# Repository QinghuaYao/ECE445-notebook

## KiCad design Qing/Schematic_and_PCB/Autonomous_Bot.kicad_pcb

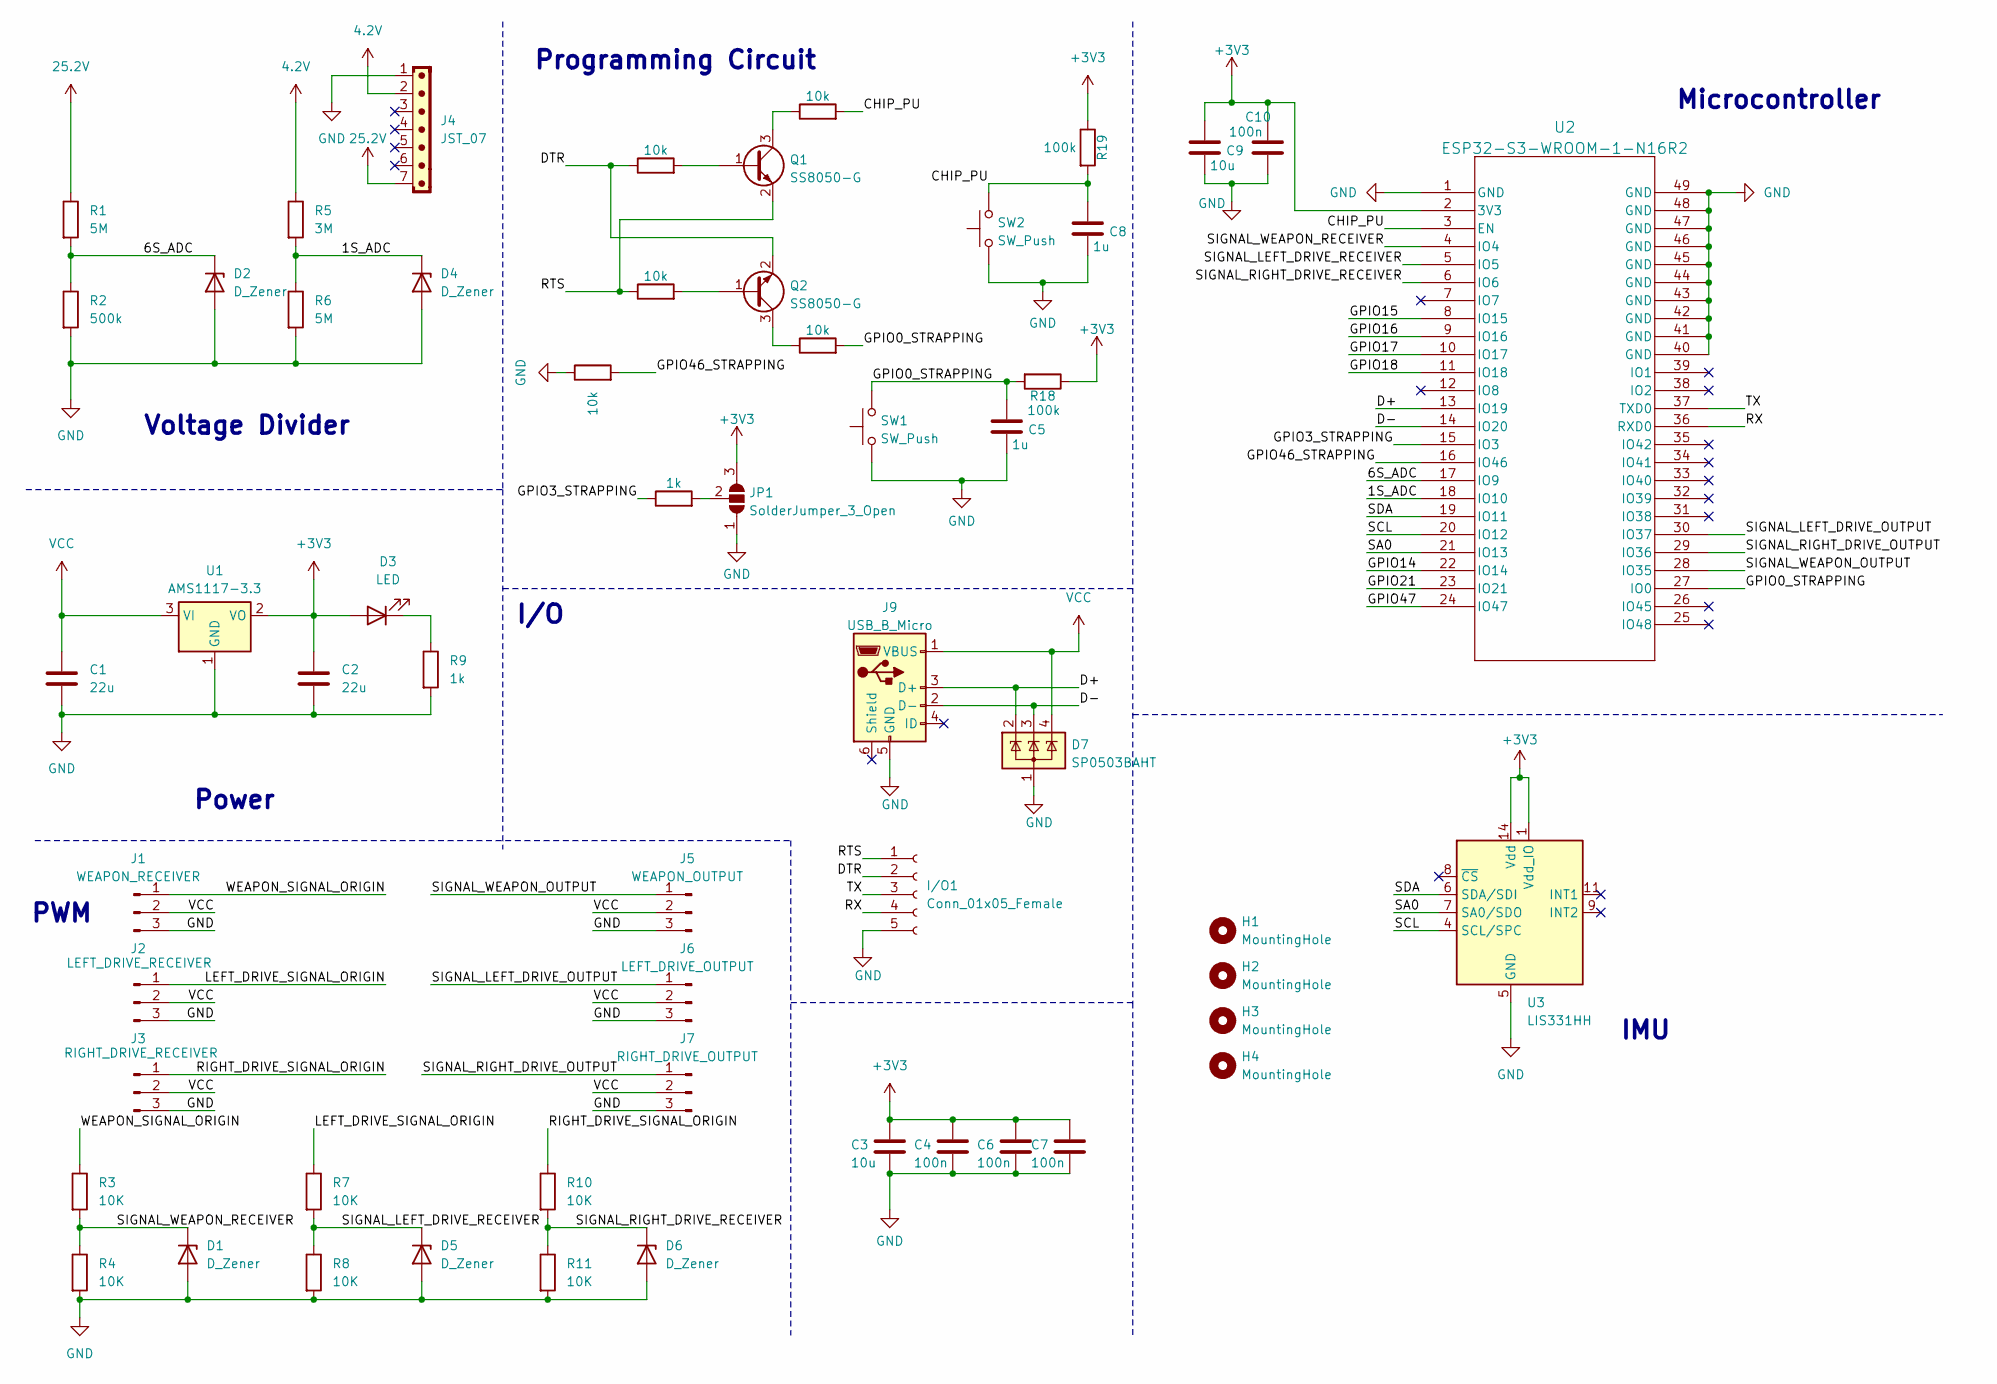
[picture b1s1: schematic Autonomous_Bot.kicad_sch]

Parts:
C1, C2: 22u; C_0603_1608Metric
C3: 10u; C_0603_1608Metric
C4, C6, C7: 100n; C_0603_1608Metric
C5, C8: 1u; C_0603_1608Metric
C9: 10u; C_0805_2012Metric
C10: 100n; C_0805_2012Metric
D1, D2, D4, D5, D6: D_Zener; D_0603_1608Metric
D3: LED; LED_0603_1608Metric
D7: SP0503BAHT; SOT-143
H1, H2, H3, H4: MountingHole; MountingHole_2.2mm_M2
I/O1: Conn_01x05_Female; PinHeader_1x05_P2.54mm_Vertical
J1: WEAPON_RECEIVER; PinHeader_1x03_P2.54mm_Vertical
J2: LEFT_DRIVE_RECEIVER; PinHeader_1x03_P2.54mm_Vertical
J3: RIGHT_DRIVE_RECEIVER; PinHeader_1x03_P2.54mm_Vertical
J4: JST_07; JST_EH_B7B-EH-A_1x07_P2.50mm_Vertical
J5: WEAPON_OUTPUT; PinHeader_1x03_P2.54mm_Vertical
J6: LEFT_DRIVE_OUTPUT; PinHeader_1x03_P2.54mm_Vertical
J7: RIGHT_DRIVE_OUTPUT; PinHeader_1x03_P2.54mm_Vertical
J9: USB_B_Micro; USB_Micro-B_Amphenol_10118194_Horizontal
JP1: SolderJumper_3_Open; SolderJumper-3_P2.0mm_Open_TrianglePad1.0x1.5mm
Q1, Q2: SS8050-G; SOT-23
R1, R6: 5M; R_1206_3216Metric
R2: 500k; R_0805_2012Metric
R3, R4, R7, R8, R10, R11: 10K; R_1206_3216Metric
R5: 3M; R_0603_1608Metric
R9: 1k; R_0603_1608Metric
R12, R13, R14, R16, R17: 10k; R_0805_2012Metric
R15: 1k; R_0805_2012Metric
R18: 100k; R_0805_2012Metric
R19: 100k; R_0603_1608Metric
SW1, SW2: SW_Push; SW_SPST_B3S-1000
U1: AMS1117-3.3; SOT-223-3_TabPin2
U2: ESP32-S3-WROOM-1-N16R2; ESP32-S3-WROOM-1_EXP
U3: LIS331HH; LGA-16_3x3mm_P0.5mm_LayoutBorder3x5y

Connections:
4.2V: J4.2, R5.1
25.2V: J4.7, R1.1
+3V3: C2.1, C3.1, C4.1, C6.1, C7.1, C9.1, C10.1, D3.2 (A), JP1.3 (B), R18.1, R19.1, U1.2 (VO), U2.2 (3V3), U3.1 (Vdd_IO), U3.14 (Vdd), U3.15 (Vdd)
/1S_ADC: D4.1 (K), R5.2, R6.1, U2.18 (IO10)
/6S_ADC: D2.1 (K), R1.2, R2.1, U2.17 (IO9)
/CHIP_PU: C8.1, R16.2, R19.2, SW2.2, U2.3 (EN)
/D+: D7.2 (K), J9.3 (D+), U2.13 (IO19)
/D-: D7.3 (K), J9.2 (D-), U2.14 (IO20)
/DTR: I/O1.2, Q2.2 (E), R13.1
/GPIO0_STRAPPING: C5.1, R17.2, R18.2, SW1.2, U2.27 (IO0)
/GPIO3_STRAPPING: R15.1, U2.15 (IO3)
/GPIO14: U2.22 (IO14)
/GPIO15: U2.8 (IO15)
/GPIO16: U2.9 (IO16)
/GPIO17: U2.10 (IO17)
/GPIO18: U2.11 (IO18)
/GPIO21: U2.23 (IO21)
/GPIO46_STRAPPING: R12.2, U2.16 (IO46)
/GPIO47: U2.24 (IO47)
/LEFT_DRIVE_SIGNAL_ORIGIN: J2.1, R7.1
/RIGHT_DRIVE_SIGNAL_ORIGIN: J3.1, R10.1
/RTS: I/O1.1, Q1.2 (E), R14.1
/RX: I/O1.4, U2.36 (RXD0)
/SA0: U2.21 (IO13), U3.7 (SA0/SDO)
/SCL: U2.20 (IO12), U3.4 (SCL/SPC)
/SDA: U2.19 (IO11), U3.6 (SDA/SDI)
/SIGNAL_LEFT_DRIVE_OUTPUT: J6.1, U2.30 (IO37)
/SIGNAL_LEFT_DRIVE_RECEIVER: D5.1 (K), R7.2, R8.1, U2.5 (IO5)
/SIGNAL_RIGHT_DRIVE_OUTPUT: J7.1, U2.29 (IO36)
/SIGNAL_RIGHT_DRIVE_RECEIVER: D6.1 (K), R10.2, R11.1, U2.6 (IO6)
/SIGNAL_WEAPON_OUTPUT: J5.1, U2.28 (IO35)
/SIGNAL_WEAPON_RECEIVER: D1.1 (K), R3.2, R4.1, U2.4 (IO4)
/TX: I/O1.3, U2.37 (TXD0)
/WEAPON_SIGNAL_ORIGIN: J1.1, R3.1
GND: C1.2, C2.2, C3.2, C4.2, C5.2, C6.2, C7.2, C8.2, C9.2, C10.2, D1.2 (A), D2.2 (A), D4.2 (A), D5.2 (A), D6.2 (A), D7.1 (A), I/O1.5, J1.3, J2.3, J3.3, J4.1, J5.3, J6.3, J7.3, J9.5 (GND), JP1.1 (A), R2.2, R4.2, R6.2, R8.2, R9.2, R11.2, R12.1, SW1.1, SW2.1, U1.1 (GND), U2.1 (GND), U2.40 (GND), U2.41 (GND), U2.42 (GND), U2.43 (GND), U2.44 (GND), U2.45 (GND), U2.46 (GND), U2.47 (GND), U2.48 (GND), U2.49 (GND), U3.5 (GND), U3.10 (GND), U3.12 (GND), U3.13 (GND), U3.16 (GND)
unnamed: D3.1 (K), R9.1
unnamed: JP1.2 (C), R15.2
unnamed: Q1.1 (B), R13.2
unnamed: Q1.3 (C), R16.1
unnamed: Q2.1 (B), R14.2
unnamed: Q2.3 (C), R17.1
VCC: C1.1, D7.4 (K), J1.2, J2.2, J3.2, J5.2, J6.2, J7.2, J9.1 (VBUS), U1.3 (VI)

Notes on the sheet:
Power
IMU
Programming Circuit
Microcontroller
PWM
I/O
Voltage Divider

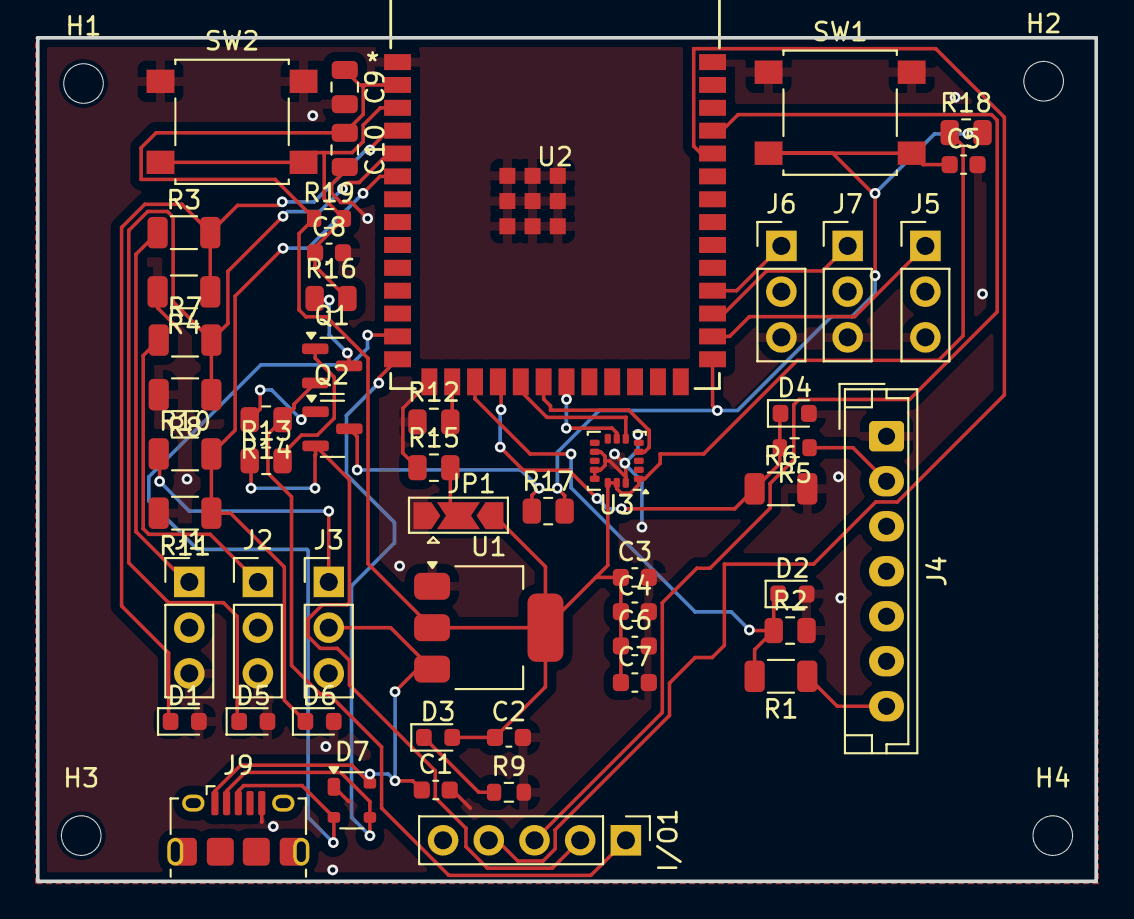
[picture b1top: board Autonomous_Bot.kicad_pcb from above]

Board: 2 copper layers, 58.8 x 46.9 mm, 57 parts (0 on the bottom side), 35 nets.

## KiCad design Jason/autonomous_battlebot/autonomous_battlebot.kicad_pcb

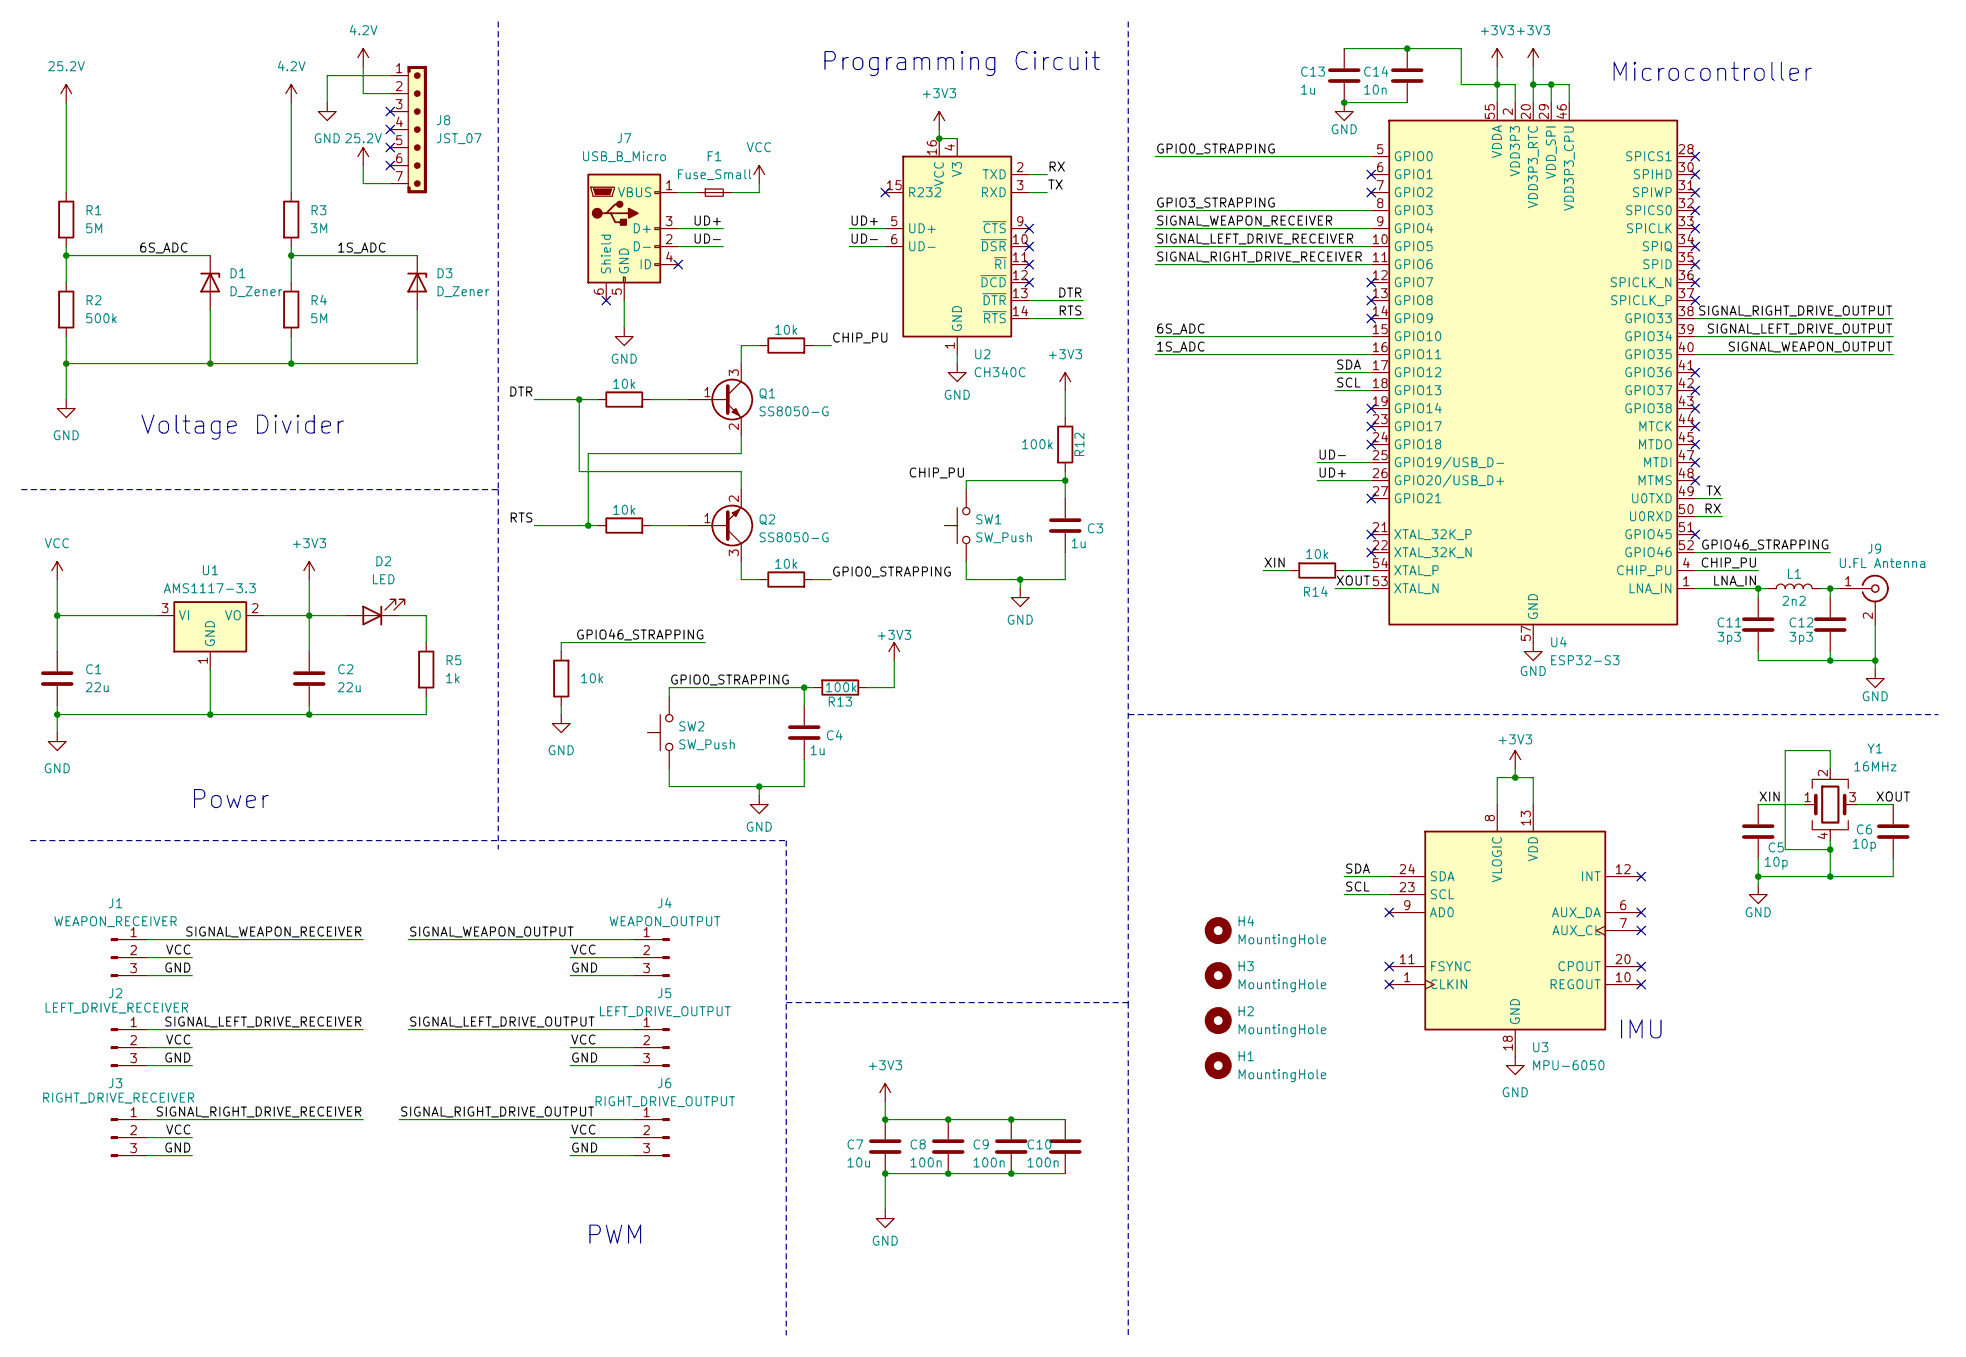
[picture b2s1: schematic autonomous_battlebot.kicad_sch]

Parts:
C1, C2: 22u; C_0603_1608Metric
C3, C4, C13: 1u; C_0603_1608Metric
C5, C6: 10p; C_0603_1608Metric
C7: 10u; C_0603_1608Metric
C8, C9, C10: 100n; C_0603_1608Metric
C11, C12: 3p3; C_0603_1608Metric
C14: 10n; C_0603_1608Metric
D1, D3: D_Zener; D_0603_1608Metric
D2: LED; LED_0603_1608Metric
F1: Fuse_Small; Fuse_0603_1608Metric
H1, H2, H3, H4: MountingHole; MountingHole_2.2mm_M2
J1: WEAPON_RECEIVER; PinHeader_1x03_P2.54mm_Vertical
J2: LEFT_DRIVE_RECEIVER; PinHeader_1x03_P2.54mm_Vertical
J3: RIGHT_DRIVE_RECEIVER; PinHeader_1x03_P2.54mm_Vertical
J4: WEAPON_OUTPUT; PinHeader_1x03_P2.54mm_Vertical
J5: LEFT_DRIVE_OUTPUT; PinHeader_1x03_P2.54mm_Vertical
J6: RIGHT_DRIVE_OUTPUT; PinHeader_1x03_P2.54mm_Vertical
J7: USB_B_Micro; USB_Micro-B_Molex-105017-0001
J8: JST_07; JST_EH_B7B-EH-A_1x07_P2.50mm_Vertical
J9: U.FL Antenna; U.FL_Molex_MCRF_73412-0110_Vertical
L1: 2n2; L_0603_1608Metric
Q1, Q2: SS8050-G; SOT-23
R1, R4: 5M; R_1206_3216Metric
R2: 500k; R_0805_2012Metric
R3: 3M; R_0603_1608Metric
R5: 1k; R_0603_1608Metric
R7, R8, R9, R10, R11, R14: 10k; R_0805_2012Metric
R12: 100k; R_0603_1608Metric
R13: 100k; R_0805_2012Metric
SW1, SW2: SW_Push; SW_SPST_B3S-1000
U1: AMS1117-3.3; SOT-223-3_TabPin2
U2: CH340C; SOIC-16_3.9x9.9mm_P1.27mm
U3: MPU-6050; InvenSense_QFN-24_4x4mm_P0.5mm
U4: ESP32-S3; QFN-56-1EP_7x7mm_P0.4mm_EP4x4mm
Y1: 16MHz; Crystal_SMD_3225-4Pin_3.2x2.5mm

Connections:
4.2V: J8.2, R3.1
25.2V: J8.7, R1.1
+3V3: C2.1, C7.1, C8.1, C9.1, C10.1, C13.1, C14.1, D2.2 (A), R12.1, R13.1, U1.2 (VO), U2.4 (V3), U2.16 (VCC), U3.8 (VLOGIC), U3.13 (VDD), U4.2 (VDD3P3), U4.3 (VDD3P3), U4.20 (VDD3P3_RTC), U4.29 (VDD_SPI), U4.46 (VDD3P3_CPU), U4.55 (VDDA), U4.56 (VDDA)
/1S_ADC: D3.1 (K), R3.2, R4.1, U4.16 (GPIO11)
/6S_ADC: D1.1 (K), R1.2, R2.1, U4.15 (GPIO10)
/CHIP_PU: C3.1, R10.2, R12.2, SW1.2, U4.4 (CHIP_PU)
/DTR: Q2.2 (E), R7.1, U2.13 (~DTR)
/GPIO0_STRAPPING: C4.1, R11.2, R13.2, SW2.2, U4.5 (GPIO0)
/GPIO3_STRAPPING: U4.8 (GPIO3)
/GPIO46_STRAPPING: R9.2, U4.52 (GPIO46)
/LNA_IN: C11.1, L1.1, U4.1 (LNA_IN)
/RTS: Q1.2 (E), R8.1, U2.14 (~RTS)
/RX: U2.2 (TXD), U4.50 (U0RXD)
/SCL: U3.23 (SCL), U4.18 (GPIO13)
/SDA: U3.24 (SDA), U4.17 (GPIO12)
/SIGNAL_LEFT_DRIVE_OUTPUT: J5.1, U4.39 (GPIO34)
/SIGNAL_LEFT_DRIVE_RECEIVER: J2.1, U4.10 (GPIO5)
/SIGNAL_RIGHT_DRIVE_OUTPUT: J6.1, U4.38 (GPIO33)
/SIGNAL_RIGHT_DRIVE_RECEIVER: J3.1, U4.11 (GPIO6)
/SIGNAL_WEAPON_OUTPUT: J4.1, U4.40 (GPIO35)
/SIGNAL_WEAPON_RECEIVER: J1.1, U4.9 (GPIO4)
/TX: U2.3 (RXD), U4.49 (U0TXD)
/UD+: J7.3 (D+), U2.5 (UD+), U4.26 (GPIO20/USB_D+)
/UD-: J7.2 (D-), U2.6 (UD-), U4.25 (GPIO19/USB_D-)
/XIN: C5.1, R14.2, Y1.1
/XOUT: C6.1, U4.53 (XTAL_N), Y1.3
GND: C1.2, C2.2, C3.2, C4.2, C5.2, C6.2, C7.2, C8.2, C9.2, C10.2, C11.2, C12.2, C13.2, C14.2, D1.2 (A), D3.2 (A), J1.3, J2.3, J3.3, J4.3, J5.3, J6.3, J7.5 (GND), J8.1, J9.2 (Ext), R2.2, R4.2, R5.2, R9.1, SW1.1, SW2.1, U1.1 (GND), U2.1 (GND), U3.18 (GND), U4.57 (GND), Y1.2, Y1.4
unnamed: D2.1 (K), R5.1
unnamed: F1.1, J7.1 (VBUS)
unnamed: C12.1, J9.1 (In), L1.2
unnamed: Q1.1 (B), R7.2
unnamed: Q1.3 (C), R10.1
unnamed: Q2.1 (B), R8.2
unnamed: Q2.3 (C), R11.1
unnamed: R14.1, U4.54 (XTAL_P)
VCC: C1.1, F1.2, J1.2, J2.2, J3.2, J4.2, J5.2, J6.2, U1.3 (VI)

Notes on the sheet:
PWM
Microcontroller
Programming Circuit
Power
Voltage Divider
IMU

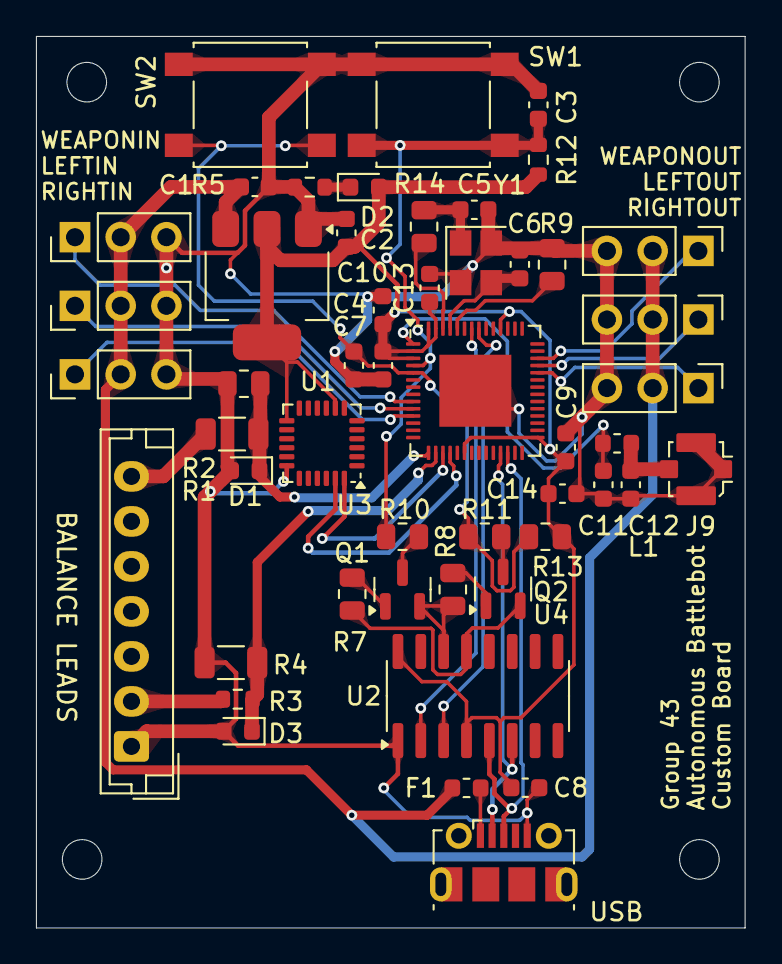
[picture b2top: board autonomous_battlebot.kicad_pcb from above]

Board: 2 copper layers, 39.4 x 49.5 mm, 54 parts (0 on the bottom side), 35 nets.

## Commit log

2025-02-11 note created!
2025-02-25 update notebook
2025-03-03 PCB upload #1
2025-03-11 initial apriltags demo
2025-03-21 autonomous subsystem code file upload 3/21
2025-03-27 code update 3/26/25
2025-03-31 notebook
2025-04-23 Update arduino_client.ino 4/22
2025-05-01 final upload 5/1
2025-05-08 Update Qing's Notebook
2025-05-09 final
